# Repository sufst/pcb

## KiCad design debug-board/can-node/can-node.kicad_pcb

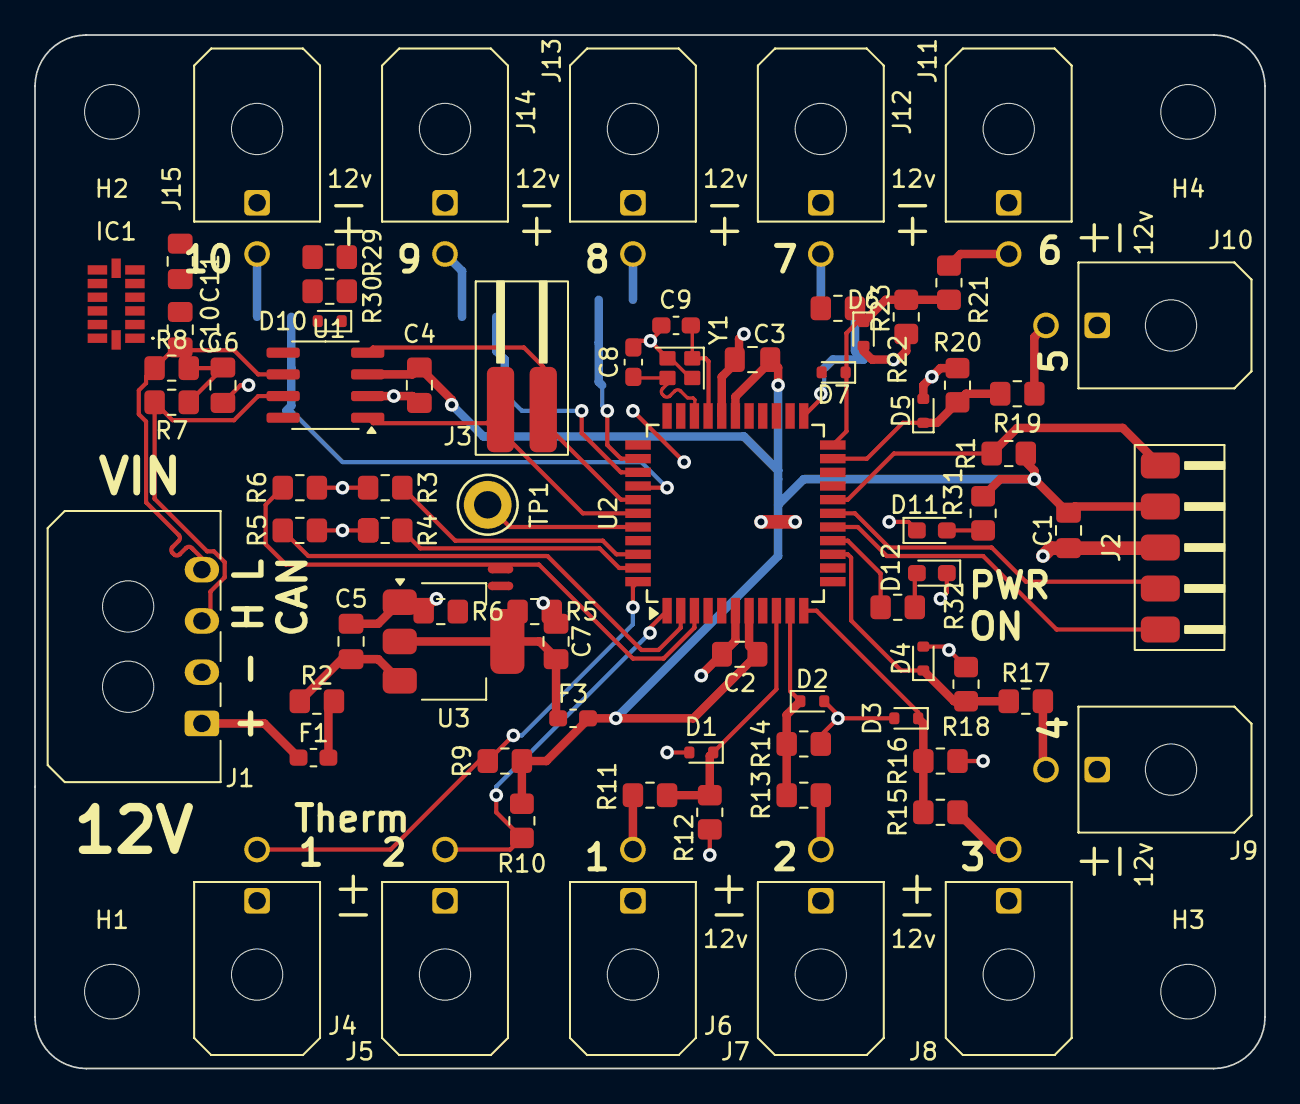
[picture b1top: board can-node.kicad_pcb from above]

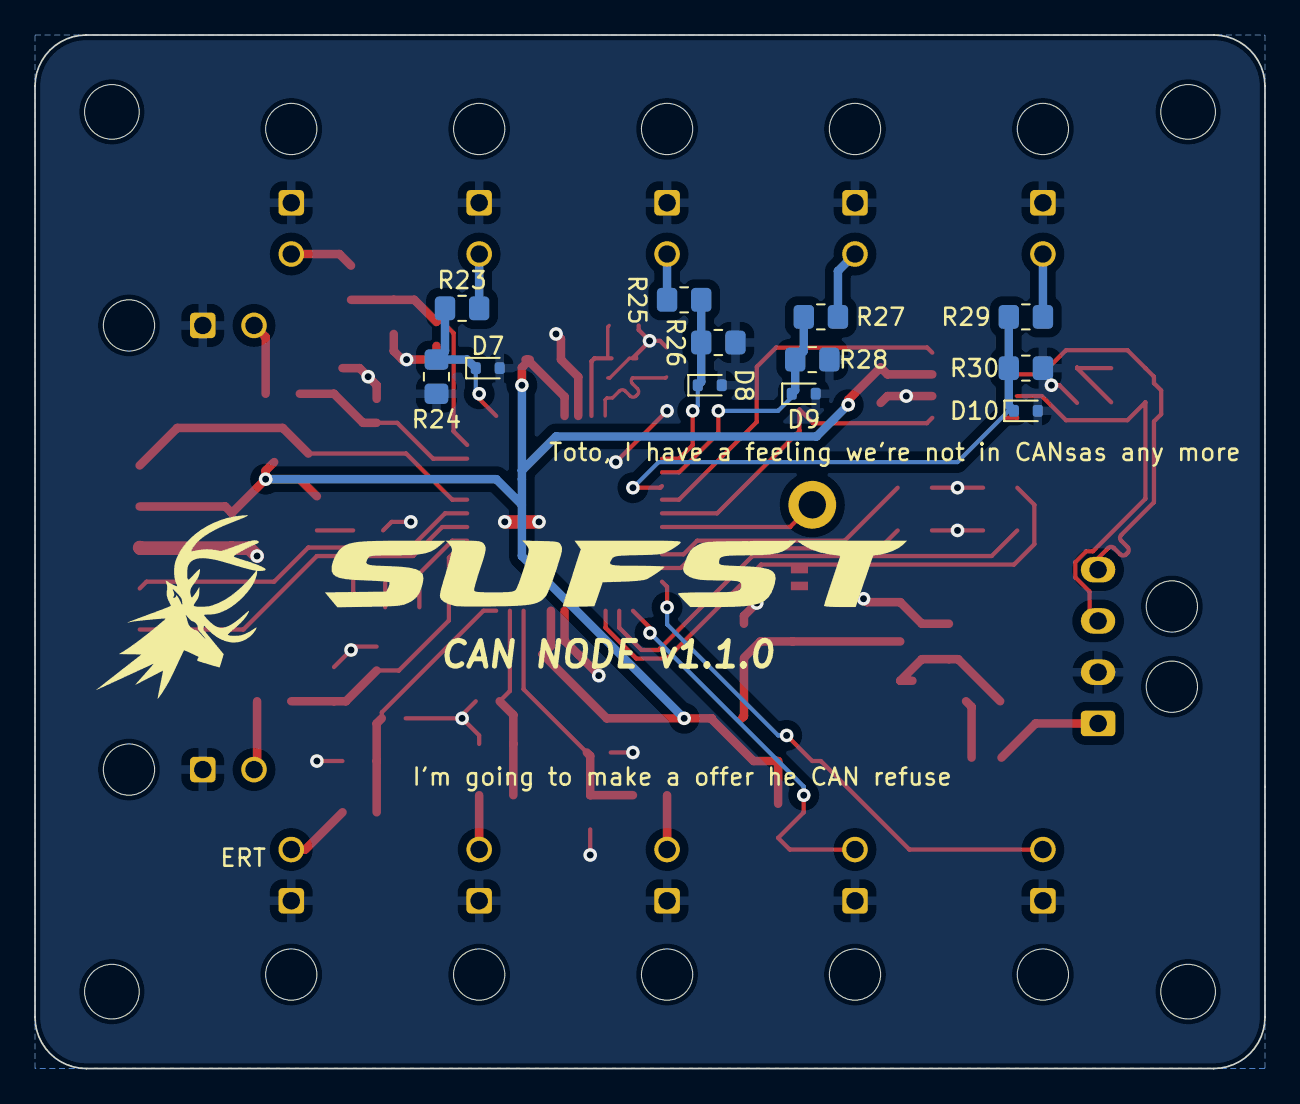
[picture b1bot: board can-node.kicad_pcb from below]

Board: 2 copper layers, 72.0 x 60.5 mm, 91 parts (12 on the bottom side), 52 nets.

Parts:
C1, C5, C7: 10u; C_0805_2012Metric_Pad1.18x1.45mm_HandSolder
C2, C3, C4: 100n; C_0805_2012Metric_Pad1.18x1.45mm_HandSolder
C6: 4n7; C_0805_2012Metric_Pad1.18x1.45mm_HandSolder
C8, C9: 10p; C_0603_1608Metric_Pad1.08x0.95mm_HandSolder
C10: 1u; C_0805_2012Metric_Pad1.18x1.45mm_HandSolder
C11: 0.1u; C_0805_2012Metric_Pad1.18x1.45mm_HandSolder
D1, D2, D3, D4, D5, D6, D7, D7#2, D8, D9, D10, D10#2: BZT585B3V3T-7; D_SOD-523
D11: RED LED; LED_0603_1608Metric_Pad1.05x0.95mm_HandSolder
D12: GREEN LED; LED_0603_1608Metric_Pad1.05x0.95mm_HandSolder
F1, F3: F0603E0R25FSTR\INT; Fuse_0603_1608Metric_Pad1.05x0.95mm_HandSolder
H1, H2, H3, H4: M3; MountingHole_3.2mm_M3
IC1: ADXL343BCCZ-RL; ADXL343BCCZRL
J1: Conn_01x04_Pin; Molex_Micro-Fit_3.0_43650-0400_1x04_P3.00mm_Horizontal
J2: Conn_01x05_Pin; Conn5_SMD
J3: Conn_01x02 Surface; Conn2_SMD
J4, J5, J6, J7, J8, J9, J10, J11, J12, J13, J14, J15: Conn_01x02_Pin; Molex_Micro-Fit_3.0_43045-0200_2x01_P3.00mm_Horizontal
NT1, NT2: NetTie_2; NetTie-2_SMD_Pad0.5mm
R1, R9, R10, R12, R14, R16, R18, R20, R22, R24, R26, R28, R30, R30#2: 10k; R_0805_2012Metric_Pad1.20x1.40mm_HandSolder
R2, R32: 12; R_0805_2012Metric_Pad1.20x1.40mm_HandSolder
R3, R4, R5, R5#2, R6, R6#2: 0; R_0805_2012Metric_Pad1.20x1.40mm_HandSolder
R7, R8: 60R; R_0805_2012Metric_Pad1.20x1.40mm_HandSolder
R11, R13, R15, R17, R19, R21, R23, R23#2, R25, R27, R29, R29#2: 40k; R_0805_2012Metric_Pad1.20x1.40mm_HandSolder
R31: 68; R_0805_2012Metric_Pad1.20x1.40mm_HandSolder
TP1: TestPoint; TestPoint_Keystone_5010-5014_Multipurpose
U1: TCAN332DR; SOIC-8_3.9x4.9mm_P1.27mm
U2: PIC18F47Q84-I/PT; TQFP-44_10x10mm_P0.8mm
U3: AZ1117CH-3.3TRG1; SOT-223-3_TabPin2
Y1: 20MHz; Crystal_SMD_SeikoEpson_FA128-4Pin_2.0x1.6mm

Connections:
+3V3: C1.1, C2.1, C3.1, C4.2, C11.1, F3.2, IC1.6 (VS), J2.2, R1.2, R9.2, R10.2, R31.2, U1.3 (VDD), U2.7 (VDD), U2.28 (VDD)
+12V: C5.1, R2.2, U3.3 (VI)
/4:1 P/D 1: D1.1 (K), R11.1, R12.2, U2.9 (RB1)
/4:1 P/D 2: D2.1 (K), R13.1, R14.2, U2.10 (RB2)
/4:1 P/D 3: D3.1 (K), R15.1, R16.2, U2.11 (RB3)
/4:1 P/D 4: D4.1 (K), R17.1, R18.2, U2.14 (RB4)
/4:1 P/D 5: D5.1 (K), R19.1, R20.2, U2.20 (RA1)
/4:1 P/D 6: D6.1 (K), R21.1, R22.2, U2.21 (RA2)
/4:1 P/D 7: D7.1 (K), D7#2.1 (K), R4.2, R23.1, R23#2.1, R24.2, U2.22 (RA3)
/4:1 P/D 8: D8.1 (K), R25.1, R26.2, U2.35 (RC1)
/4:1 P/D 9: D9.1 (K), R27.1, R28.2, U2.36 (RC2)
/4:1 P/D 10: D10.1 (K), D10#2.1 (K), R29.1, R29#2.1, R30.2, R30#2.2, U2.5 (RD7)
/ASDI1: IC1.13 (SDA/SDI/SDIO), NT2.2
/ASDO1: IC1.12 (SDO/ALT_ADDRESS), NT1.2
/CAN+: J1.3, R7.2, U1.7 (CANH)
/CAN-: J1.4, R8.1, U1.6 (CANL)
/CAN_RX: J3.2, U1.4 (RXD), U2.38 (RD0)
/CAN_TX: J3.1, U1.1 (TXD), U2.39 (RD1)
/CLK+: C8.1, U2.31 (RA6), Y1.3
/CLK-: C9.1, U2.30 (RA7), Y1.1
/Config value 0: R3.1, R5#2.1, U2.3 (RD5)
/Config value 1: R4.1, R6#2.1, U2.4 (RD6)
/Decoupling: C6.1, R7.1, R8.2
/ICSPCLK: J2.5, U2.16 (RB6)
/ICSPDAT: J2.4, U2.17 (RB7)
/INT1: IC1.8 (INT1), U2.23 (RA4)
/Power ON LED: R32.2, U2.15 (RB5)
/SCK1: IC1.14 (SCL/SCLK), U2.37 (RC3)
/SD01: NT2.1, U2.43 (RC5)
/SDI1: NT1.1, U2.42 (RC4)
/Therm 1: J4.2, R9.1, U2.1 (RC7)
/Therm 2: J5.2, R10.1, U2.2 (RD4)
/Unfused 3V3: C7.1, F3.1, U3.2 (VO)
/VCC IO: C10.1, IC1.1 (VDD_I/O), U2.32 (RC0)
/~CS: IC1.7 (~CS), U2.24 (RA5)
/~MCLR: J2.1, R1.1, U2.18 (RE3)
GND: C1.2, C2.2, C3.2, C4.1, C5.2, C6.2, C7.2, C8.2, C9.2, C10.2, C11.2, D1.2 (A), D2.2 (A), D3.2 (A), D4.2 (A), D5.2 (A), D6.2 (A), D7.2 (A), D7#2.2 (A), D8.2 (A), D9.2 (A), D10.2 (A), D10#2.2 (A), D11.1 (K), D12.1 (K), IC1.2 (GND_1), IC1.4 (GND_2), IC1.5 (GND_3), J1.2, J2.3, J4.1, J5.1, J6.1, J7.1, J8.1, J9.1, J10.1, J11.1, J12.1, J13.1, J14.1, J15.1, R3.2, R4.2, R5.2, R5#2.2, R6.2, R6#2.2, R12.1, R14.1, R16.1, R18.1, R20.1, R22.1, R24.1, R26.1, R28.1, R30.1, R30#2.1, U1.2 (GND), U2.6 (VSS), U2.29 (VSS), U3.1 (GND), Y1.2, Y1.4
unnamed: D11.2 (A), R31.1
unnamed: D12.2 (A), R32.1
unnamed: F1.2, R2.1
unnamed: F1.1, J1.1
unnamed: J6.2, R11.2
unnamed: J7.2, R13.2
unnamed: J8.2, R15.2
unnamed: J9.2, R17.2
unnamed: J10.2, R19.2
unnamed: J11.2, R21.2
unnamed: J12.2, R23.2, R23#2.2
unnamed: J13.2, R25.2
unnamed: J14.2, R27.2
unnamed: J15.2, R29.2, R29#2.2
unnamed: TP1.1, U2.40 (RD2)

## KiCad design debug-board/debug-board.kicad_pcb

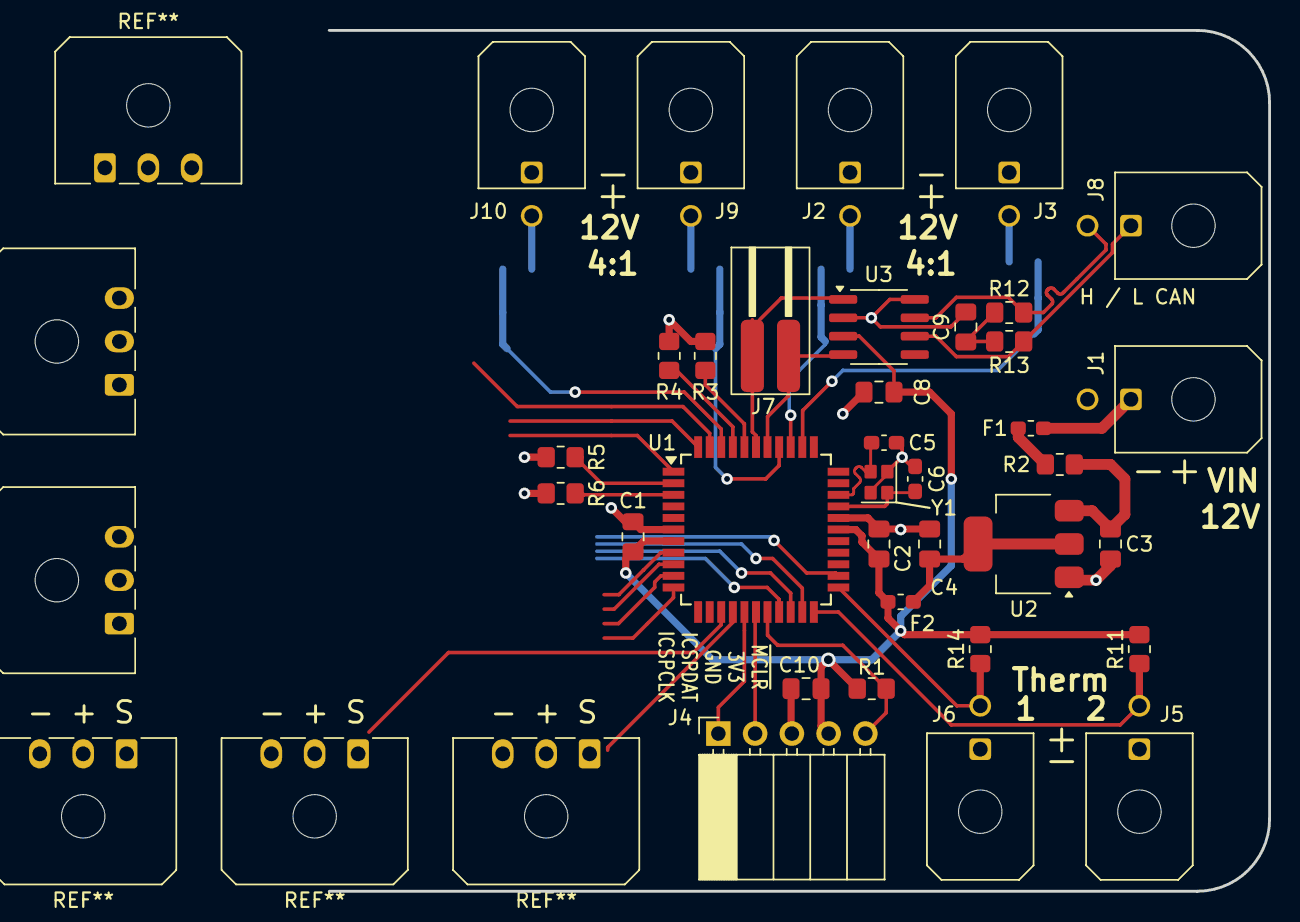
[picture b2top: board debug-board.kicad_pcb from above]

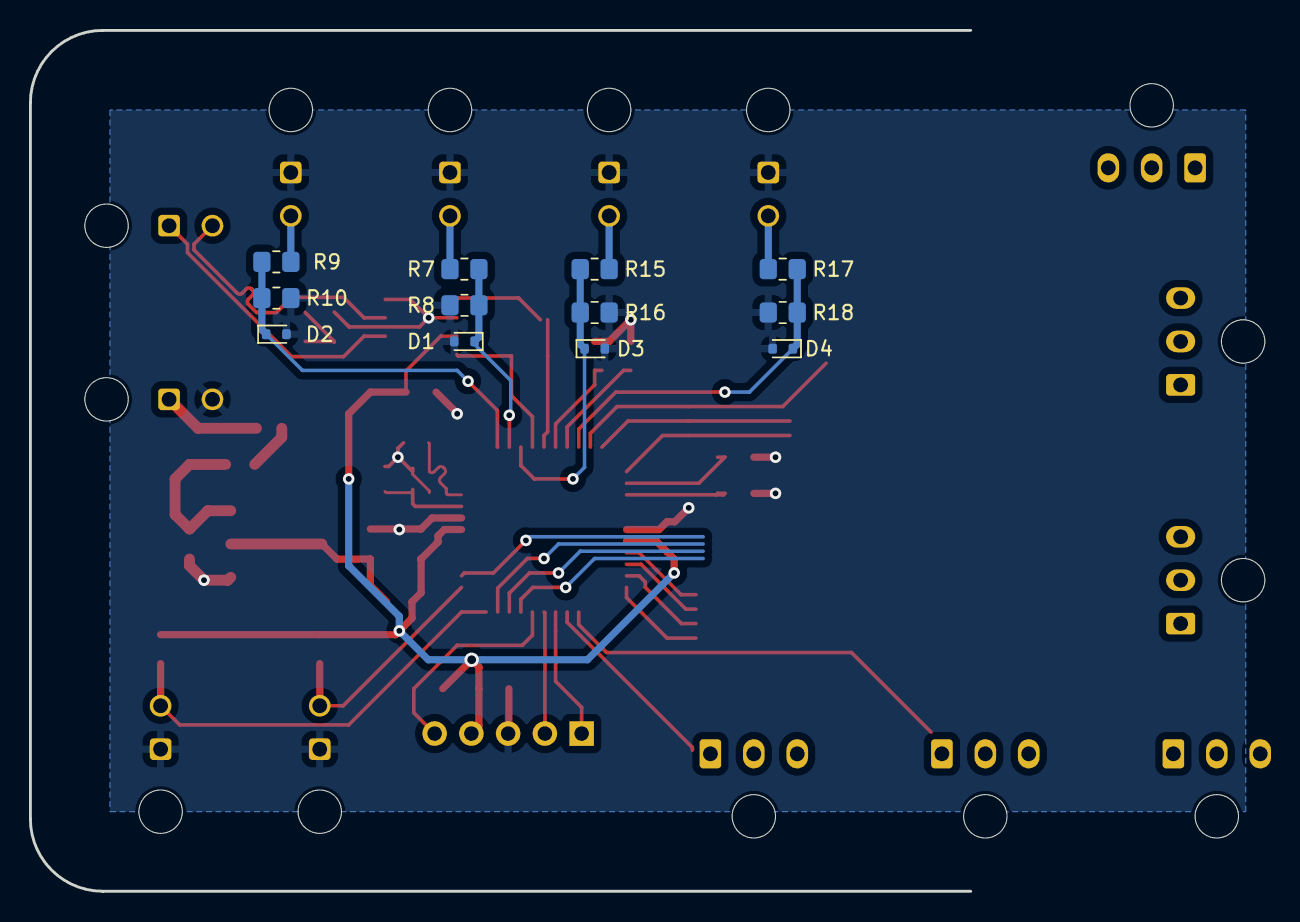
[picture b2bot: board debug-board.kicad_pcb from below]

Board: 2 copper layers, 65.0 x 59.5 mm, 47 parts (12 on the bottom side), 30 nets.

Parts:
C1, C2, C8: 100n; C_0805_2012Metric_Pad1.18x1.45mm_HandSolder
C3, C4, C10: 10u; C_0805_2012Metric_Pad1.18x1.45mm_HandSolder
C5, C6: 10p; C_0603_1608Metric_Pad1.08x0.95mm_HandSolder
C9: 4n7; C_0805_2012Metric_Pad1.18x1.45mm_HandSolder
D1, D2, D3, D4: BZT585B3V3T-7; D_SOD-523
F1, F2: T0603FF0250TM; Fuse_0603_1608Metric_Pad1.05x0.95mm_HandSolder
J1, J2, J3, J5, J6, J8, J9, J10: Conn_01x02_Pin; Molex_Micro-Fit_3.0_43045-0200_2x01_P3.00mm_Horizontal
J4: Conn_01x05_Pin; PinSocket_1x05_P2.54mm_Horizontal
J7: Conn_01x02_Pin; Conn2_SMD
R1, R8, R10, R11, R14, R16, R18: 10k; R_0805_2012Metric_Pad1.20x1.40mm_HandSolder
R2: 12; R_0805_2012Metric_Pad1.20x1.40mm_HandSolder
R3, R4, R5, R6: 0; R_0805_2012Metric_Pad1.20x1.40mm_HandSolder
R7, R9, R15, R17: 40k; R_0805_2012Metric_Pad1.20x1.40mm_HandSolder
R12, R13: 60R; R_0805_2012Metric_Pad1.20x1.40mm_HandSolder
U1: PIC18F47Q84-I/PT; TQFP-44_10x10mm_P0.8mm
U2: AZ1117CH-3.3TRG1; SOT-223-3_TabPin2
U3: MAX3051ESA+; SOIC-8_3.9x4.9mm_P1.27mm
Y1: 40MHz; Crystal_SMD_SeikoEpson_FA128-4Pin_2.0x1.6mm

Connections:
+3V3: C1.1, C2.1, C8.2, C10.1, F2.2, J4.4, R1.2, R11.2, R14.2, U1.7 (VDD), U1.28 (VDD), U3.3 (VDD)
+12V: C3.1, R2.2, U2.3 (VI)
/4:1 P/D 1: D1.1 (K), R7.1, R8.2, U1.36 (RC2)
/4:1 P/D 2: D2.1 (K), R9.1, R10.2, U1.35 (RC1)
/4:1 P/D 3: D3.1 (K), R15.1, R16.2, U1.37 (RC3)
/4:1 P/D 4: D4.1 (K), R17.1, R18.2, U1.42 (RC4)
/CAN+: J8.2, R12.2, U3.7 (CANH)
/CAN-: J8.1, R13.1, U3.6 (CANL)
/CAN_RX: J7.2, U1.38 (RD0), U3.4 (RXD)
/CAN_TX: J7.1, U1.39 (RD1), U3.1 (TXD)
/CLK+: C5.1, U1.31 (RA6), Y1.3
/CLK-: C6.1, U1.30 (RA7), Y1.1
/Decoupling: C9.1, R12.1, R13.2
/ICSPCLK: J4.1, U1.16 (RB6)
/ICSPDAT: J4.2, U1.17 (RB7)
/Therm 1: J6.2, R14.1, U1.23 (RA4)
/Therm 2: J5.2, R11.1, U1.22 (RA3)
/Unfused 3V3: C4.1, F2.1, U2.2 (VO)
/~MCLR: J4.5, R1.1, U1.18 (RE3)
GND: C1.2, C2.2, C3.2, C4.2, C5.2, C6.2, C8.1, C9.2, C10.2, D1.2 (A), D2.2 (A), D3.2 (A), D4.2 (A), J1.2, J2.1, J3.1, J4.3, J5.1, J6.1, J9.1, J10.1, R3.2, R4.2, R5.2, R6.2, R8.1, R10.1, R16.1, R18.1, U1.6 (VSS), U1.29 (VSS), U2.1 (GND), U3.2 (GND), U3.8 (RS), Y1.2, Y1.4
unnamed: F1.2, R2.1
unnamed: F1.1, J1.1
unnamed: J2.2, R7.2
unnamed: J3.2, R9.2
unnamed: J9.2, R15.2
unnamed: J10.2, R17.2
unnamed: R3.1, U1.40 (RD2)
unnamed: R4.1, U1.41 (RD3)
unnamed: R5.1, U1.2 (RD4)
unnamed: R6.1, U1.3 (RD5)

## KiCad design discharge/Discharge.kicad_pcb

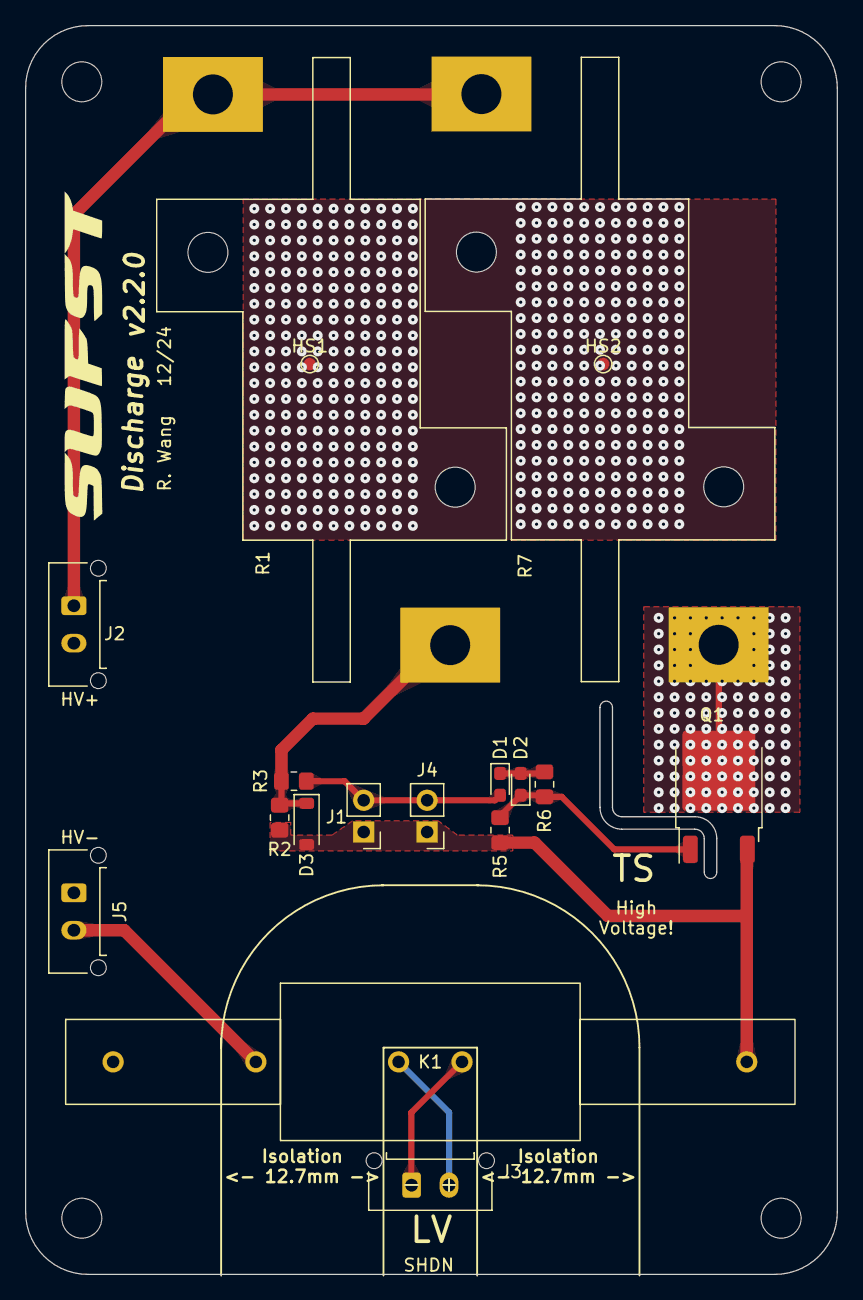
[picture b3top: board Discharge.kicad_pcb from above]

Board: 2 copper layers, 65.0 x 100.0 mm, 22 parts (0 on the bottom side), 11 nets.

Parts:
D1, D2: LED; LED_0603_1608Metric_Pad1.05x0.95mm_HandSolder
D3: MMSZ5250BT1G; D_SOD-123
H1, H2, H3, H4: MountingHole; MountingHole_3.2mm_M3
HS1, HS2: Heatsink; TestPoint_Pad_D1.0mm
J1: THERM_RES; PinHeader_1x02_P2.54mm_Vertical
J2: HV+; Molex_Micro-Fit_3.0_43650-0215_1x02_P3.00mm_Vertical
J3: SHUT; Molex_Micro-Fit_3.0_43650-0215_1x02_P3.00mm_Vertical
J4: THERM_MOSFET; PinHeader_1x02_P2.54mm_Vertical
J5: HV-; Molex_Micro-Fit_3.0_43650-0215_1x02_P3.00mm_Vertical
K1: pickering-67-1-c
Q1: IPD80R4K5P7; TO-252-2
R1: 30k; HSA25
R2: 30k; R_0805_2012Metric_Pad1.20x1.40mm_HandSolder
R3: 27k; R_0805_2012Metric_Pad1.20x1.40mm_HandSolder
R5: 100k; R_0805_2012Metric_Pad1.20x1.40mm_HandSolder
R6: 0; R_0805_2012Metric_Pad1.20x1.40mm_HandSolder
R7: 2.7k; HSA25

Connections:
/HEATSINK: HS1.1, HS2.1
/HV+: J2.1, R1.1, R7.1
/HV-: J5.2, K1.2
/RLY_H: D3.2 (A), J1.1, J4.1, K1.7, Q1.3 (S), R2.2, R5.2
/SHUT+: J3.2, K1.3
/SHUT-: J3.1, K1.5
unnamed: D1.2 (A), J1.2, J4.2, R3.2
unnamed: D1.1 (K), D2.2 (A), R6.1
unnamed: D2.1 (K), Q1.1 (G), R5.1, R6.2
unnamed: D3.1 (K), R1.2, R2.1, R3.1
unnamed: Q1.2 (D), R7.2

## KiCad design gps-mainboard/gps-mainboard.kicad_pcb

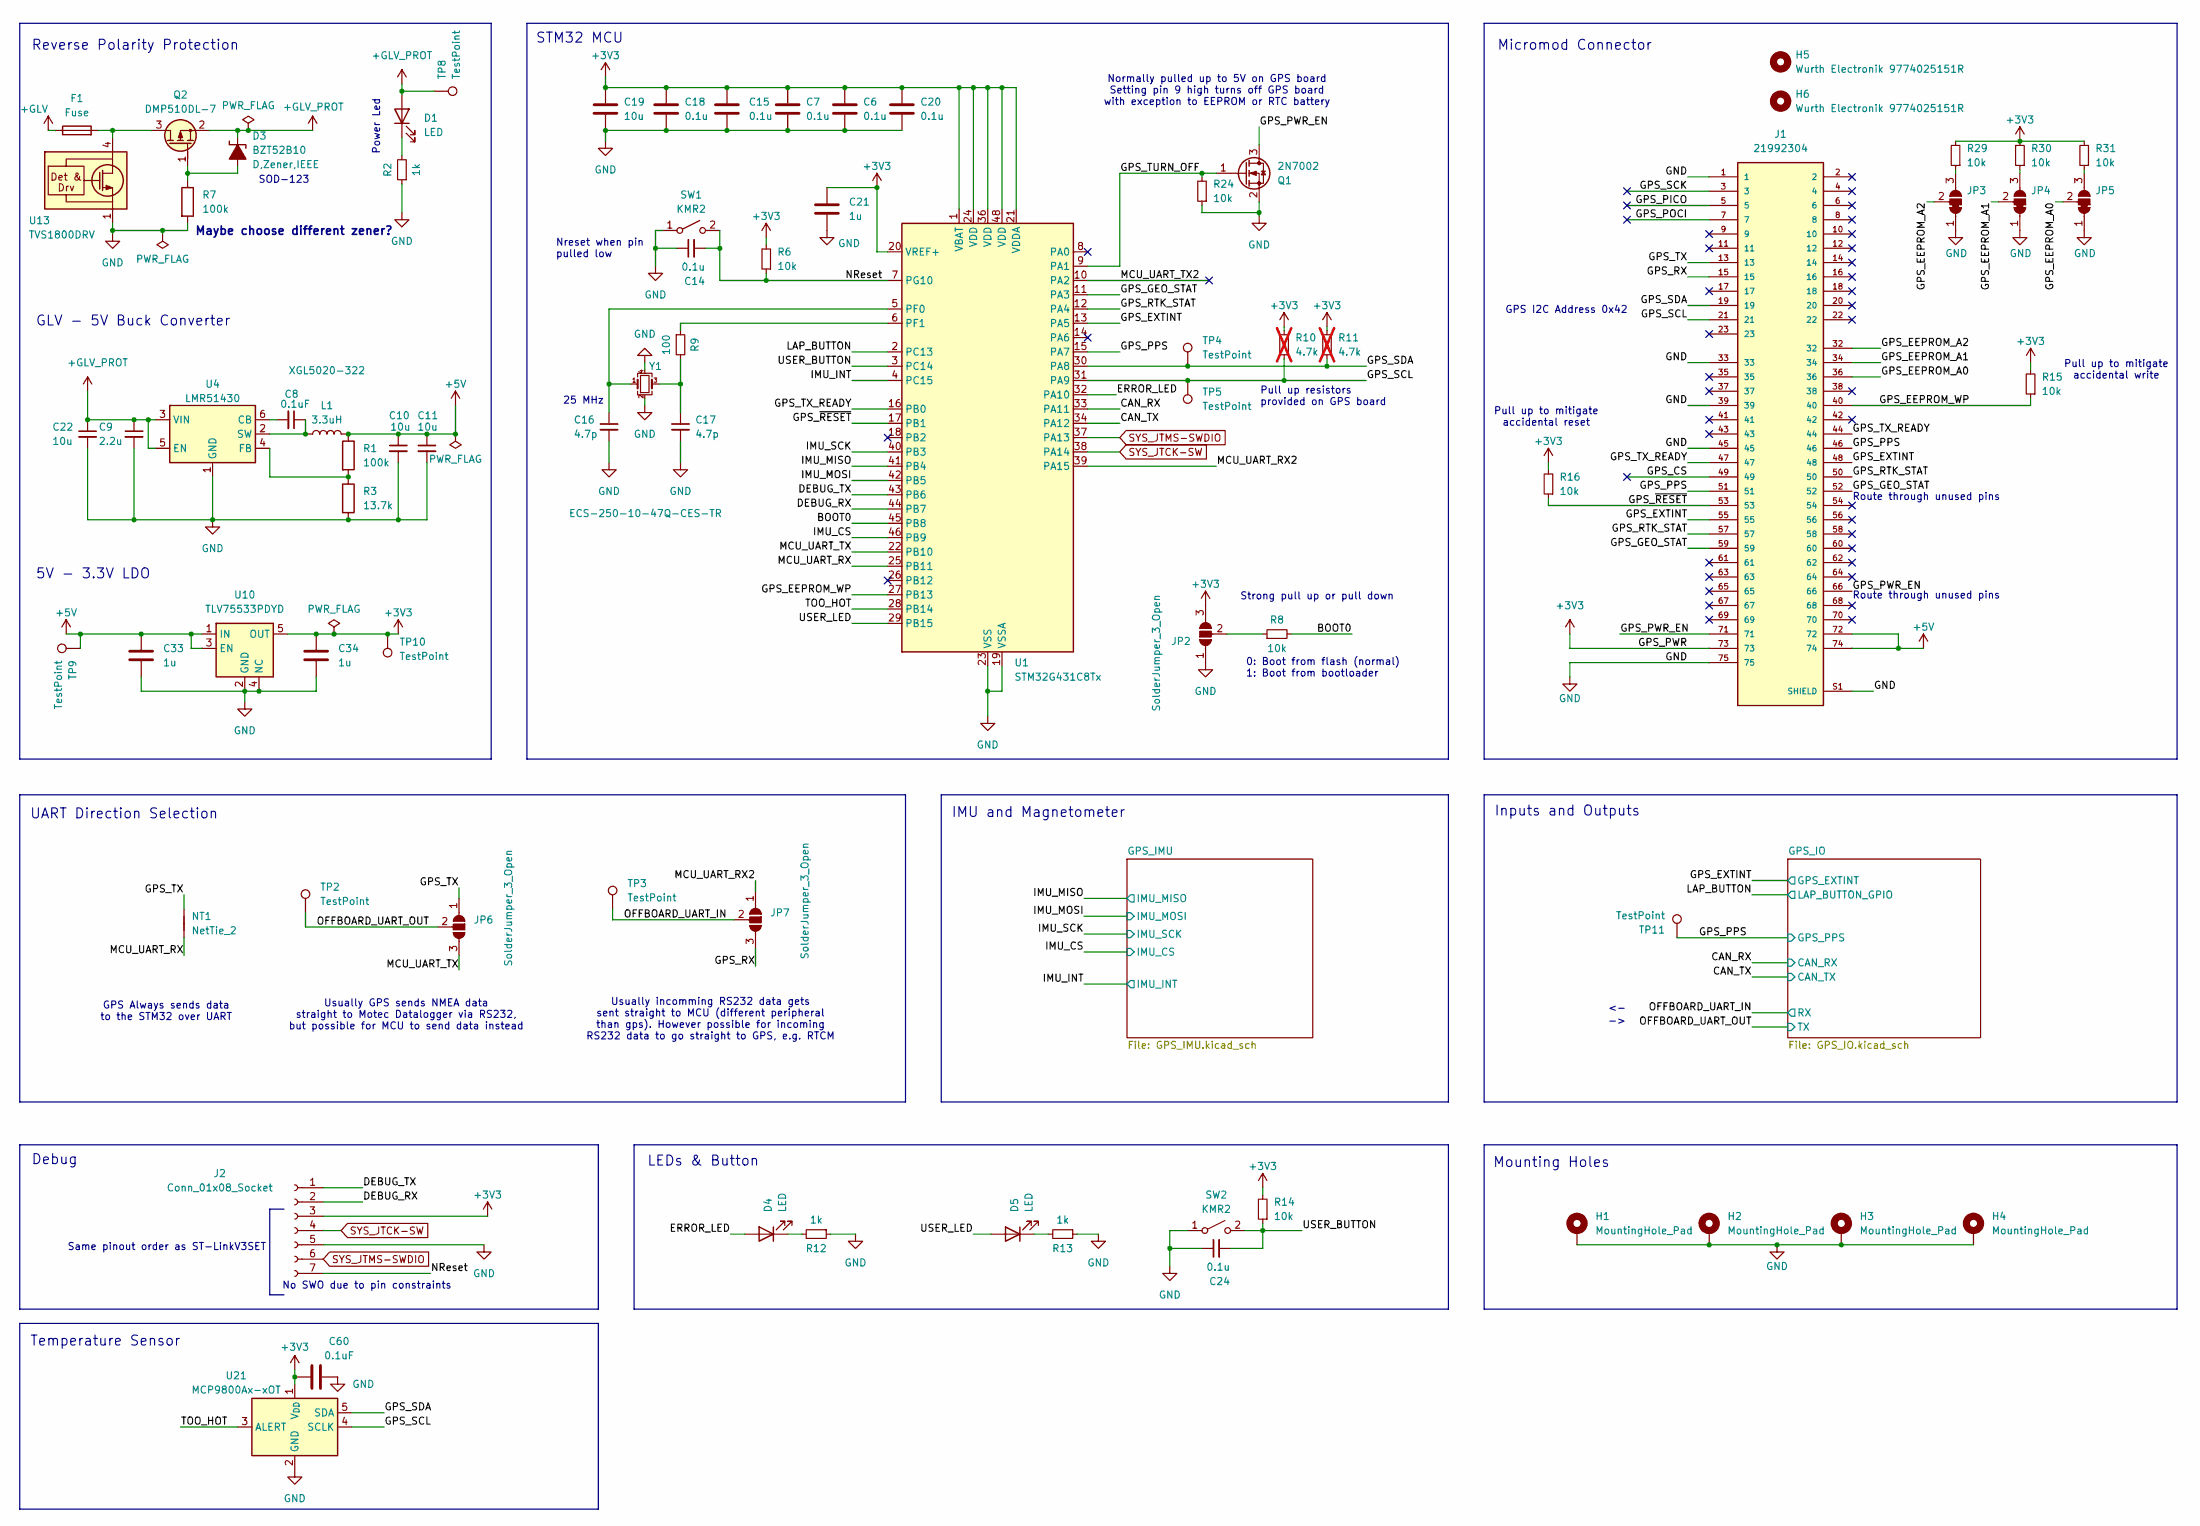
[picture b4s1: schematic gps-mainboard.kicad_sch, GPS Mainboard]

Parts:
C6, C7, C14, C15, C18, C20, C24: 0.1u; C_0603_1608Metric_Pad1.08x0.95mm_HandSolder; MPN CL10B104KB85PNL
C8: 0.1uF; C_0603_1608Metric_Pad1.08x0.95mm_HandSolder; MPN CL10B104KB85PNL
C9: 2.2u; C_0603_1608Metric_Pad1.08x0.95mm_HandSolder; MPN TMK107ABJ225KA-T
C10, C11: 10u; C_0805_2012Metric_Pad1.18x1.45mm_HandSolder; MPN CL10A106MA8NRWC
C16, C17: 4.7p; C_0603_1608Metric_Pad1.08x0.95mm_HandSolder; MPN 0402N4R7C500CT
C19, C22: 10u; C_0603_1608Metric_Pad1.08x0.95mm_HandSolder; MPN CL10A106MA8NRWC
C21, C33, C34: 1u; C_0603_1608Metric_Pad1.08x0.95mm_HandSolder; MPN UMK107BJ105KA-T
C60: 0.1uF; C_0603_1608Metric_Pad1.08x0.95mm_HandSolder; MPN CL10B104KB85PNL; Mouser Order Number 81-GRM155R62A104KE4J
D1, D4, D5: LED; LED_0603_1608Metric_Pad1.05x0.95mm_HandSolder
D3: BZT52B10; D_SOD-123; MPN BZT52B10
F1: Fuse; Fuse_0603_1608Metric_Pad1.05x0.95mm_HandSolder
H1, H2, H3, H4: MountingHole_Pad; MountingHole_3.2mm_M3_Pad_Via
H5, H6: Wurth Electronik 9774025151R; 9774025151R; MPN 9774025151R
J1: 21992304; TE_21992304; MPN 21992304
J2: Conn_01x08_Socket; PinSocket_1x07_P2.54mm_Vertical
JP2, JP6, JP7: SolderJumper_3_Open; SolderJumper-3_P1.3mm_Open_RoundedPad1.0x1.5mm
JP3, JP4, JP5: SolderJumper_3_Bridged12; SolderJumper-3_P1.3mm_Bridged12_RoundedPad1.0x1.5mm
L1: 3.3uH; L_Coilcraft_XAL5020-XXX; MPN XGL5020-322
NT1: NetTie_2; NetTie-2_SMD_Pad0.5mm
Q1: 2N7002; SOT-23; MPN XP262N7002TR-G
Q2: DMP510DL-7; SOT-23; MPN DMP510DL
R1, R7: 100k; R_0603_1608Metric_Pad0.98x0.95mm_HandSolder; MPN RT0603FRE10100KL
R2, R12, R13: 1k; R_0603_1608Metric_Pad0.98x0.95mm_HandSolder; MPN RNCP0603FTD1K00
R3: 13.7k; R_0603_1608Metric_Pad0.98x0.95mm_HandSolder; MPN RT0603FRE0713K7L
R6, R8, R14, R15, R16, R24, R29, R30, R31: 10k; R_0603_1608Metric_Pad0.98x0.95mm_HandSolder; MPN RT0603RF1310KL
R9: 100; R_0603_1608Metric_Pad0.98x0.95mm_HandSolder; MPN RT0603FRE07100RL
R10, R11: 4.7k; R_0603_1608Metric_Pad0.98x0.95mm_HandSolder; MPN RC0603FR-074K7P; not fitted
SW1, SW2: KMR2; SW_Push_1P1T_NO_CK_KMR2; MPN KMR221NG LFS
TP2, TP3, TP4, TP5, TP8, TP9, TP10, TP11: TestPoint; Keystone 5015; MPN 5015
U1: STM32G431C8Tx; LQFP-48_7x7mm_P0.5mm; MPN STM32G431C8Tx
U4: LMR51430; SOT-23-6; MPN LMR51430YDDCR
U10: TLV75533PDYD; MPN TLV75533PDYD
U13: TVS1800DRV; WSON-6-1EP_2x2mm_P0.65mm_EP1x1.6mm; MPN TVS1800DRV
U21: MCP9800Ax-xOT; SOT-23-5; MPN MCP9800A5T-M/OT; Mouser Order Number 579-MCP9800A5T-M/OT
Y1: ECS-250-10-47Q-CES-TR; Resonator_SMD_ECS_ECX-1247Q_1.6x1.2x0.3mm; MPN ECS-250-10-47Q-CES-TR

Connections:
+3V3: C6.1, C7.1, C15.1, C18.1, C19.1, C20.1, C21.1, C34.1, C60.1, J1.73, J2.3, JP2.3 (B), R6.2, R10.2, R11.2, R14.2, R15.2, R16.2, R29.2, R30.2, R31.2, TP10.1, U1.1 (VBAT), U1.20 (VREF+), U1.21 (VDDA), U1.24 (VDD), U1.36 (VDD), U1.48 (VDD), U10.5 (OUT), U21.1 (V_{DD}); also elsewhere on the board
+5V: C10.1, C11.1, C33.1, J1.72, J1.74, L1.2, R1.1, TP9.1, U10.1 (IN), U10.3 (EN)
+GLV: F1.1; also elsewhere on the board
+GLV_PROT: C9.1, C22.1, D1.2 (A), D3.1 (K-), Q2.2 (S), TP8.1, U4.3 (VIN), U4.5 (EN); also elsewhere on the board
/BOOT0: R8.2, U1.45 (PB8)
/CAN_RX: U1.33 (PA11); also elsewhere on the board
/CAN_TX: U1.34 (PA12); also elsewhere on the board
/DEBUG_RX: J2.2, U1.44 (PB7)
/DEBUG_TX: J2.1, U1.43 (PB6)
/ERROR_LED: D4.2 (A), U1.32 (PA10)
/GPS_CS: J1.49
/GPS_EEPROM_A0: J1.36, JP5.2 (C)
/GPS_EEPROM_A1: J1.34, JP4.2 (C)
/GPS_EEPROM_A2: J1.32, JP3.2 (C)
/GPS_EEPROM_WP: J1.40, R15.1, U1.27 (PB13)
/GPS_EXTINT: J1.48, J1.55, U1.13 (PA5); also elsewhere on the board
/GPS_GEO_STAT: J1.52, J1.59, U1.11 (PA3)
/GPS_PICO: J1.5
/GPS_POCI: J1.7
/GPS_PPS: J1.46, J1.51, TP11.1, U1.15 (PA7); also elsewhere on the board
/GPS_PWR_EN: J1.66, J1.71, Q1.3 (D)
/GPS_RTK_STAT: J1.50, J1.57, U1.12 (PA4)
/GPS_RX: J1.15, JP7.3 (B)
/GPS_SCK: J1.3
/GPS_SCL: J1.21, R10.1, TP5.1, U1.31 (PA9), U21.4 (SCLK)
/GPS_SDA: J1.19, R11.1, TP4.1, U1.30 (PA8), U21.5 (SDA)
/GPS_TURN_OFF: Q1.1 (G), R24.2, U1.9 (PA1)
/GPS_TX: J1.13, JP6.1 (A), NT1.2
/GPS_TX_READY: J1.44, J1.47, U1.16 (PB0)
/GPS_~RESET: J1.53, R16.1, U1.17 (PB1)
/IMU_CS: U1.46 (PB9); also elsewhere on the board
/IMU_INT: U1.4 (PC15); also elsewhere on the board
/IMU_MISO: U1.41 (PB4); also elsewhere on the board
/IMU_MOSI: U1.42 (PB5); also elsewhere on the board
/IMU_SCK: U1.40 (PB3); also elsewhere on the board
/LAP_BUTTON: U1.2 (PC13); also elsewhere on the board
/MCU_UART_RX: NT1.1, U1.25 (PB11)
/MCU_UART_RX2: JP7.1 (A), U1.39 (PA15)
/MCU_UART_TX: JP6.3 (B), U1.22 (PB10)
/MCU_UART_TX2: U1.10 (PA2)
/NReset: C14.2, J2.7, R6.1, SW1.2 (B), U1.7 (PG10)
/OFFBOARD_UART_IN: JP7.2 (C), TP3.1; also elsewhere on the board
/OFFBOARD_UART_OUT: JP6.2 (C), TP2.1; also elsewhere on the board
/TOO_HOT: U1.28 (PB14), U21.3 (ALERT)
/USER_BUTTON: C24.2, R14.1, SW2.2 (B), U1.3 (PC14)
/USER_LED: D5.2 (A), U1.29 (PB15)
GND: C6.2, C7.2, C9.2, C10.2, C11.2, C14.1, C15.2, C16.2, C17.2, C18.2, C19.2, C20.2, C21.2, C22.2, C24.1, C33.2, C34.2, C60.2, H1.1, H2.1, H3.1, H4.1, J1.1, J1.33, J1.39, J1.45, J1.75, J1.S1 (SHIELD), J1.S2 (SHIELD), J2.5, JP2.1 (A), JP3.1 (A), JP4.1 (A), JP5.1 (A), Q1.2 (S), R2.1, R3.2, R7.2, R12.1, R13.1, R24.1, SW1.1 (A), SW2.1 (A), U1.19 (VSSA), U1.23 (VSS), U1.35 (VSS), U1.47 (VSS), U4.1 (GND), U10.2 (GND), U10.4 (NC), U10.6 (GND), U13.1 (GND), U13.2 (GND), U13.3 (GND), U13.7 (GND), U21.2 (GND), Y1.2, Y1.4; also elsewhere on the board
unnamed: C17.1, R9.2, Y1.3
unnamed: D1.1 (K), R2.2
unnamed: D3.2 (A+), Q2.1 (G), R7.1
unnamed: D4.1 (K), R12.2
unnamed: D5.1 (K), R13.2
unnamed: JP2.2 (C), R8.1
unnamed: JP3.3 (B), R29.1
unnamed: JP4.3 (B), R30.1
unnamed: JP5.3 (B), R31.1
unnamed: F1.2, Q2.3 (D), U13.4 (IN), U13.5 (IN), U13.6 (IN)
unnamed: C16.1, U1.5 (PF0), Y1.1
unnamed: R9.1, U1.6 (PF1)
unnamed: C8.2, U4.6 (CB)
unnamed: R1.2, R3.1, U4.4 (FB)
unnamed: C8.1, L1.1, U4.2 (SW)
SYS_JTCK-SW: J2.4, U1.38 (PA14)
SYS_JTMS-SWDIO: J2.6, U1.37 (PA13)

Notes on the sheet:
Temperature Sensor
Route through unused pins
Strong pull up or pull down
LEDs & Button
Debug
Pull up resistors provided on GPS board
25 MHz
IMU and Magnetometer
Nreset when pin pulled low
0: Boot from flash (normal) 1: Boot from bootloader
Power Led
Same pinout order as ST-LinkV3SET
No SWO due to pin constraints
Usually incomming RS232 data gets sent straight to MCU (different peripheral than gps). However possible for incoming RS232 data to go straight to GPS, e.g. RTCM
Usually GPS sends NMEA data straight to Motec Datalogger via RS232, but possible for MCU to send data instead
Mounting Holes
Normally pulled up to 5V on GPS board Setting pin 9 high turns off GPS board with exception to EEPROM or RTC battery
SOD-123
Inputs and Outputs
5V - 3.3V LDO
GPS Always sends data to the STM32 over UART
Maybe choose different zener?
Micromod Connector
GLV - 5V Buck Converter
Pull up to mitigate accidental reset
Reverse Polarity Protection
Pull up to mitigate accidental write
UART Direction Selection
STM32 MCU
GPS I2C Address 0x42

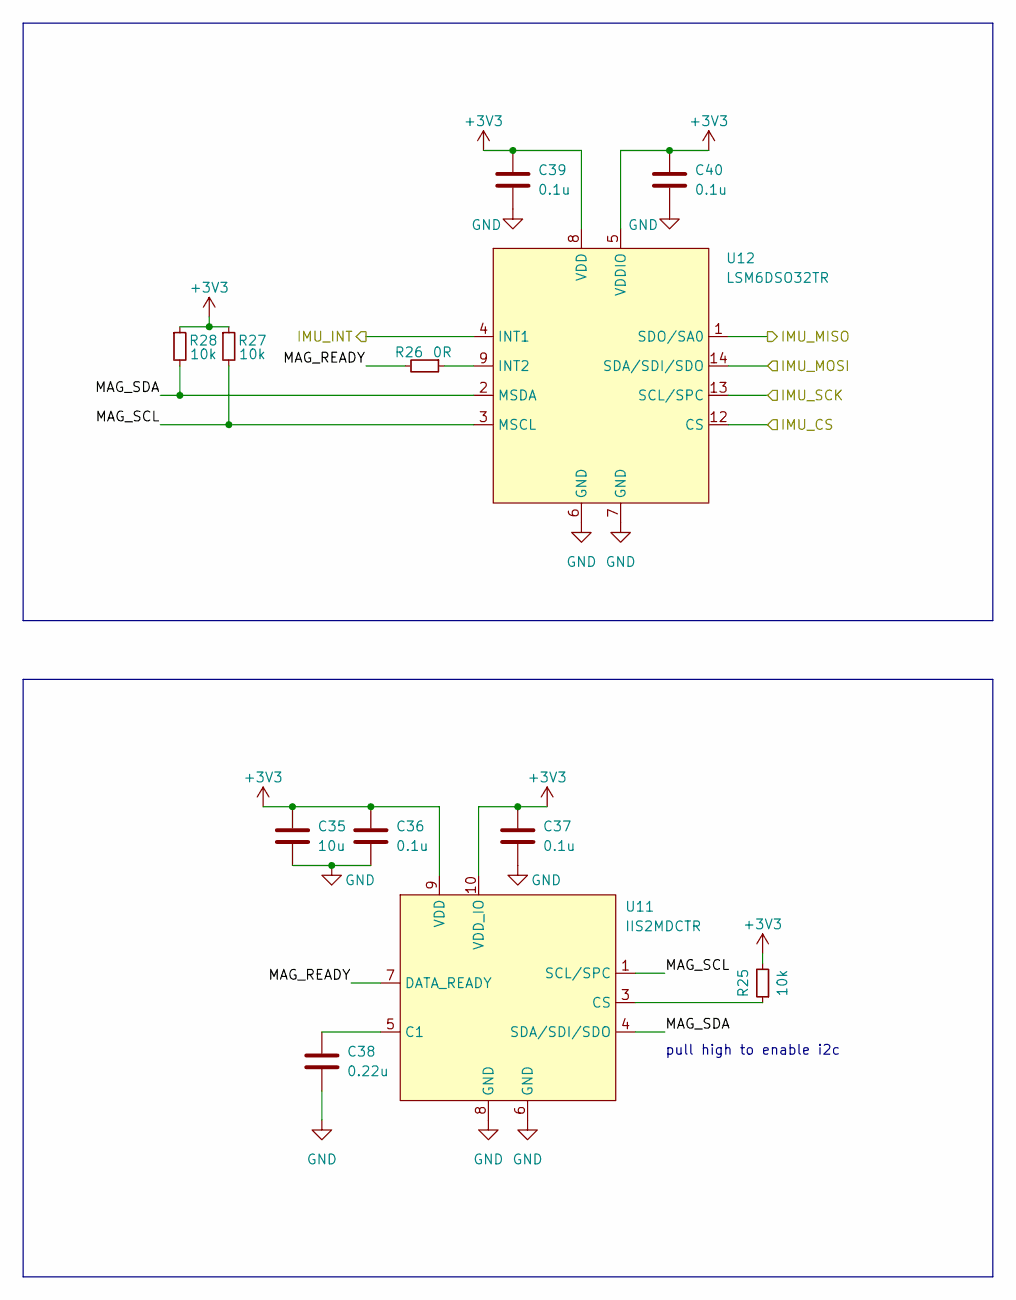
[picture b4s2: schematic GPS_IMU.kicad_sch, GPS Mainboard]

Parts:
C35: 10u; C_0603_1608Metric_Pad1.08x0.95mm_HandSolder; MPN CL10A106MA8NRWC
C36, C37, C39, C40: 0.1u; C_0603_1608Metric_Pad1.08x0.95mm_HandSolder; MPN CL10B104KB85PNL
C38: 0.22u; C_0603_1608Metric_Pad1.08x0.95mm_HandSolder; MPN 0603B224K500CT
R25, R27, R28: 10k; R_0603_1608Metric_Pad0.98x0.95mm_HandSolder; MPN RT0603RF1310KL
R26: 0R; R_0603_1608Metric_Pad0.98x0.95mm_HandSolder; MPN RC0603FR-100RL
U11: IIS2MDCTR; LGA-12_2x2mm_P0.5mm; MPN IIS2MDCTR
U12: LSM6DSO32TR; LGA-14_3x2.5mm_P0.5mm_LayoutBorder3x4y; MPN LSM6DSO32TR

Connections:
+3V3: C35.1, C36.1, C37.1, C39.1, C40.1, R25.2, R27.1, R28.1, U11.9 (VDD), U11.10 (VDD_IO), U12.5 (VDDIO), U12.8 (VDD); also elsewhere on the board
/GPS_IMU/MAG_READY: R26.2, U11.7 (DATA_READY)
/GPS_IMU/MAG_SCL: R27.2, U11.1 (SCL/SPC), U12.3 (MSCL)
/GPS_IMU/MAG_SDA: R28.2, U11.4 (SDA/SDI/SDO), U12.2 (MSDA)
/IMU_CS: U12.12 (CS); also elsewhere on the board
/IMU_INT: U12.4 (INT1); also elsewhere on the board
/IMU_MISO: U12.1 (SDO/SA0); also elsewhere on the board
/IMU_MOSI: U12.14 (SDA/SDI/SDO); also elsewhere on the board
/IMU_SCK: U12.13 (SCL/SPC); also elsewhere on the board
GND: C35.2, C36.2, C37.2, C38.2, C39.2, C40.2, U11.6 (GND), U11.8 (GND), U12.6 (GND), U12.7 (GND); also elsewhere on the board
unnamed: C38.1, U11.5 (C1)
unnamed: R25.1, U11.3 (CS)
unnamed: R26.1, U12.9 (INT2)

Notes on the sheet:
pull high to enable i2c

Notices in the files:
gps/ZED-F9K/Imported/SparkFun_GPS_ZED-F9K.kicad_sch:
https://creativecommons.org/licenses/by-sa/4.0
Released under the Creative Commons
parts and their libraries:
License: Apache-2.0
Released under the Creative Commons Attribution Share-Alike 4.0 License
